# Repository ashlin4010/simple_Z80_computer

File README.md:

# Simple Z80 Computer
The goal of this project was to build a minimally complex Z80 computer capable of running CP/M. While I haven not yet ported CP/M, it should be capable of it.

This system is made of two boards, the upper board has the the CPU, RAM, ROM and UART. The lower board has Composite Video, USB Keyboard, USB to serial converter, Compact Flash and 8 indicator LEDs.

If you want to have a better understanding of how this system works you checkout the schematics or my [blog](https://blog.tephra.me/z80_sbc/).

## Specifications ##
* 64K Static RAM
* 32K ROM
* Z80 @ 4Mhz
* USB Keyboard via Raspberry Pi Zero
* Composite Video via Raspberry Pi Zero
* HDMI Video via Raspberry Pi Zero
* Support for 27256 or AT28C256 ROM
* Compact Flash
* 8 LED indicators
* Built-in USB to serial converter @ 9600 baud

## Raspberry Pi Zero (Optional) ##
As part of the project I wanted to have a composite video output however, there was not sufficient space to have a native composite video interface. As an alternative I have used a Raspberry Pi Zero running [pigfx](https://github.com/fbergama/pigfx) which acts as a terminal emulator providing a USB keyboard input and composite video output.

### Raspberry Pi Installation ###
To the underside of the PCB solder in the Raspberry Pi using the pins from a 2.54mm header so that the Pi is flat against the PCB. Only the circles and yellow need to be soldered. Back on the top side of the PCB you will see some pads that need to be connected to some test points on the Pi, connect them using some wire cuts offs.

## ROM Jumper Configuration ##

This system supports the W27C257, 27256 and AT28C256 ROM chips. The W27C257 and 27256 are read-only and need to have jumpers set in the topmost position. The AT28C256 is read/write and needs two jumpers in the lower position.

## Software Compiler ##
My assembler of choice for this project has been the [Retro Assembler](https://enginedesigns.net/retroassembler/) by Peter Tihanyi. There is a VSCode [plugin](https://marketplace.visualstudio.com/items?itemName=EngineDesigns.retroassembler) available.

## Serial Bootloader  ##
The early version of the monitor includes a utility "sboot" that will fetch data over the UART and store it in the lower 32k and jump to the start of memory.

For the serial bootloader to work you must be running the server utility that will provide the files for sboot to load. You can find it in ``software/server``.

The sboot command can be configured to auto start on boot by setting `UART_AUTO_BOOT` to True in `monitor.z80.asm` and re-building.

## Memory Address Space ##

This system has 64K of RAM and 32K of ROM. However, the Z80 can only ever address 64K at a time. When the system starts up the top 32K of memory maps to RAM, and the lower 32K maps to ROM. The system can, when ready, swap the lower 32K of ROM for RAM.

 ## IO Address Space ##

| Address | Device        | R/W | Description             |
|---------|---------------|-----|-------------------------|
| 0x10    | SIO           | R/W | UART A Data Register    |
| 0x11    | SIO           | R   | UART A Status Register  |
| 0x12    | SIO           | R/W | UART B Data Register    |
| 0x13    | SIO           | R   | UART B Status Register  |
| 0x20    | 8-bit Latch   | W   | LED Output              |
| 0x30-37 | Compact Flash | R/W | Compact Flash Registers |
| 0x70    | Flip-flop     | W   | RAM/ROM Page            |

## Schematics ##

### Z80 Main Board Schematics - [PDF](design_files/main_board/simple_Z80.pdf) ###

### Compact Flash & Raspberry Pi Board - [PDF](design_files/CompactFlash/CompactFlash.pdf) ###

## BOM ##

### Z80 Board ##

| Id | Designator                                              | Footprint                                                          | Quantity | Designation         | Supplier and ref |   |   |
|----|---------------------------------------------------------|--------------------------------------------------------------------|----------|---------------------|------------------|---|---|
| 1  | J2                                                      | PinHeader_1x04_P2.54mm_Vertical                                    | 1        | Conn_01x04_Male     |                  |   |   |
| 2  | C3,C2,C4,C5,C17,C12,C14,C6,C7,C16,C9,C13,C8,C10,C11,C15 | C_Disc_D3.0mm_W1.6mm_P2.50mm                                       | 16       | 0.1uf               |https://www.digikey.co.nz/en/products/detail/kemet/C320C104K5R5TA7303/3726160                  |   |   |
| 3  | R2,R1,R3,R4                                             | R_Axial_DIN0204_L3.6mm_D1.6mm_P7.62mm_Horizontal                   | 4        | 2k7                 |                  |   |   |
| 4  | R5                                                      | R_Axial_DIN0204_L3.6mm_D1.6mm_P7.62mm_Horizontal                   | 1        | 1k                  |                  |   |   |
| 5  | C1                                                      | C_Disc_D3.0mm_W1.6mm_P2.50mm                                       | 1        | 150pF               |https://www.digikey.co.nz/en/products/detail/vishay-beyschlag-draloric-bc-components/K151J15C0GF5TL2/286469                  |   |   |
| 6  | U1                                                      | DIP-40_W15.24mm_Socket                                             | 1        | Z80CPU              |                  |   |   |
| 7  | U7                                                      | DIP-40_W15.24mm                                                    | 1        | Z8440               |                  |   |   |
| 8  | U14, U2                                                 | DIP-28_W15.24mm                                                    | 1        | KM62256CLP          |                  |   |   |
| 9  | U13                                                     | DIP-20_W7.62mm_Socket                                              | 1        | 74LS374             |                  |   |   |
| 10 | U5                                                      | DIP-14_W7.62mm_Socket                                              | 1        | 74LS04              |                  |   |   |
| 11 | U9                                                      | DIP-16_W7.62mm_Socket                                              | 1        | 74LS161             |                  |   |   |
| 12 | U3                                                      | DIP_Socket-28_W11.9_W12.7_W15.24_W17.78_W18.5_3M_228-1277-00-0602J | 1        | 27256               |                  |   |   |
| 13 | X1                                                      | Oscillator_DIP-8                                                   | 1        | CXO_DIP8            |https://www.digikey.co.nz/en/products/detail/abracon-llc/ACH-8-000MHZ-EK/675379                  |   |   |
| 14 | U15                                                     | TO-92                                                              | 1        | DS1233              |https://www.digikey.co.nz/en/products/detail/analog-devices-inc-maxim-integrated/DS1233-5-T-R/1017808                  |   |   |
| 15 | D2                                                      | LED_D3.0mm                                                         | 1        | LED                 |                  |   |   |
| 16 | U11,U8                                                  | DIP-14_W7.62mm_Socket                                              | 2        | 74LS74              |                  |   |   |
| 17 | SW2                                                     | SW_THT_SK-12F17-G_7-0                                              | 1        | SW_SPDT             |https://www.digikey.co.nz/en/products/detail/c-k/SK-12F17-G-7/2747163                  |   |   |
| 18 | U4                                                      | DIP-14_W7.62mm_Socket                                              | 1        | 74LS00              |                  |   |   |
| 19 | SW1                                                     | SW_PUSH_6mm_H4.3mm                                                 | 1        | SW_Push             |https://www.digikey.co.nz/en/products/detail/cui-devices/TS02-66-70-BK-160-LCR-D/15634243                  |   |   |
| 20 | U6                                                      | DIP-16_W7.62mm_Socket                                              | 1        | 74LS138             |                  |   |   |
| 21 | J1                                                      | PinSocket_2x16_P2.54mm_Vertical                                    | 1        | Conn_01x32_Pin      |                  |   |   |
| 22 | J4                                                      | BarrelJack_CUI_PJ-037A                                             | 1        | Jack-DC             |https://www.digikey.co.nz/en/products/detail/cui-devices/PJ-037A/1644545                  |   |   |
| 23 | U12                                                     | DIP-14_W7.62mm_Socket                                              | 1        | 74LS32              |                  |   |   |
| 24 | J7                                                      | PinSocket_2x06_P2.54mm_Vertical                                    | 1        | Conn_01x12_Male     |                  |   |   |
| 25 | J3                                                      | PinHeader_2x03_P2.54mm_Vertical                                    | 1        | Conn_02x03_Odd_Even |                  |   |   |

### CompactFlash ##

| Id | Designator                      | Footprint                                             | Quantity | Designation       | Supplier and ref |   |   |
|----|---------------------------------|-------------------------------------------------------|----------|-------------------|------------------|---|---|
| 1  | R2                              | R_Axial_DIN0204_L3.6mm_D1.6mm_P7.62mm_Horizontal      | 1        | 100R              |                  |   |   |
| 2  | J2                              | PinHeader_2x06_P2.54mm_Vertical                       | 1        | Conn_01x12_Male   |                  |   |   |
| 3  | J7,J8                           | SolderWirePad_1x01_SMD_1x2mm                          | 2        | Conn_01x01_Pin    |                  |   |   |
| 4  | R8,R9,R7,R10                    | R_Axial_DIN0204_L3.6mm_D1.6mm_P7.62mm_Horizontal      | 4        | 10k               |                  |   |   |
| 5  | J5                              | SWITCHCRAFT_PJRAN1X1U04X                              | 1        | RCA_Video         |https://www.digikey.co.nz/en/products/detail/switchcraft-inc/PJRAN1X1U04X/969899                         |   |   |
| 6  | U1                              | CF-Card_101D-TAAB-R01                                 | 1        | Compact_Flash     |https://www.digikey.co.nz/en/products/detail/attend-technology/101D-TAAB-R01/17633884                    |   |   |
| 7  | U2                              | DIP-20_W7.62mm                                        | 1        | 74LS541           |                  |   |   |
| 8  | Q2,Q1                           | TO-92_Inline                                          | 2        | 2N7000            |https://www.digikey.co.nz/en/products/detail/diotec-semiconductor/2N7000/13164314                        |   |   |
| 9  | D2,D8,D6,D1,D4,D7,D5,D9,D3      | LED_D3.0mm_Horizontal_O1.27mm_Z2.0mm                  | 9        | LED               |                  |   |   |
| 10 | R1,R5,R6,R3,R4                  | R_Axial_DIN0204_L3.6mm_D1.6mm_P7.62mm_Horizontal      | 5        | 1K                |                  |   |   |
| 11 | U3                              | SOP-8_3.9x4.9mm_P1.27mm                               | 1        | CH340N            |https://vi.aliexpress.com/item/1005004980156804.html                                                     |   |   |
| 12 | R19,R20                         | R_0805_2012Metric                                     | 2        | 1k                |https://www.digikey.co.nz/en/products/detail/stackpole-electronics-inc/RNCP0805FTD1K00/2240229           |   |   |
| 13 | R14,R15,R18,R11,R13,R16,R17,R12 | R_Axial_DIN0204_L3.6mm_D1.6mm_P7.62mm_Horizontal      | 8        | 1k                |                  |   |   |
| 14 | J1                              | Raspberry_Pi_Zero_Socketed_THT_FaceDown_MountingHoles | 1        | Raspberry_Pi_Zero |                  |   |   |
| 15 | J4                              | PinSocket_2x16_P2.54mm_Vertical                       | 1        | Conn_01x32_Pin    |                  |   |   |
| 16 | J6                              | USB_Mini-B_Wuerth_65100516121_Horizontal              | 1        | USB_B_Micro       |https://www.digikey.co.nz/en/products/detail/amphenol-cs-commercial-products/GMSB0532112YEU/13683104     |   |   |
| 17 | J3                              | 629104190121                                          | 1        | USB_A             |https://www.digikey.co.nz/en/products/detail/w%C3%BCrth-elektronik/629104190121/6644275                  |   |   |
| 18 | J10                             | PinSocket_1x04_P2.54mm_Vertical                       | 1        | Conn_01x04_Pin    |                  |   |   |
| 19 | C1                              | C_Disc_D3.0mm_W1.6mm_P2.50mm                          | 1        | 100pF             |                  |   |   |
| 20 | C2                              | C_0805_2012Metric                                     | 1        | 100nF             |https://www.digikey.co.nz/en/products/detail/samsung-electro-mechanics/CL21B104KBCNNNC/3886661           |   |   |

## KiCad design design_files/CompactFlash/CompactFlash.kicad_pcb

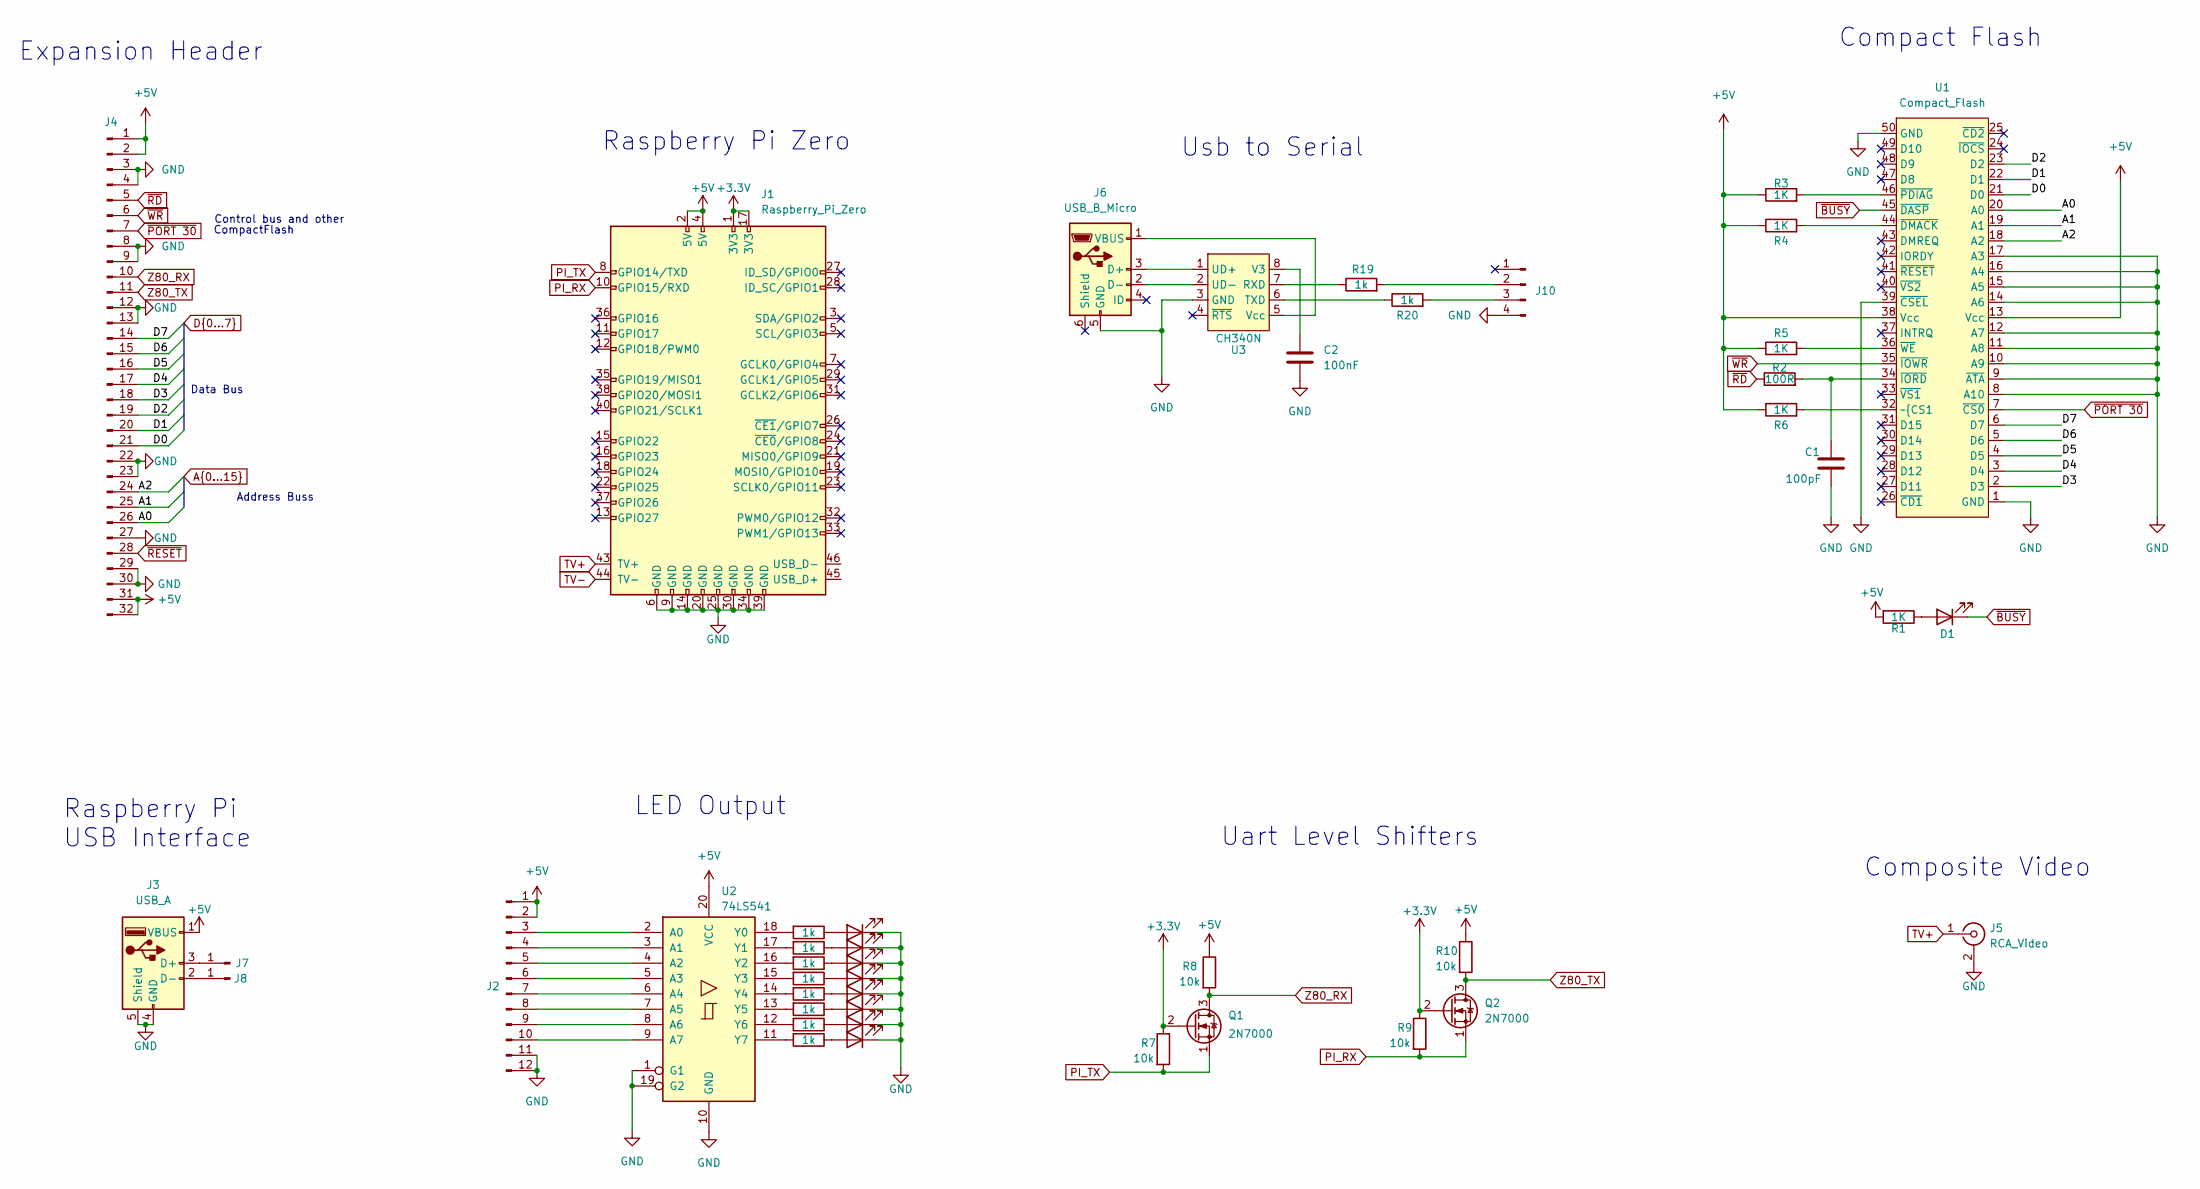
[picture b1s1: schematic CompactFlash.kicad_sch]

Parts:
C1: 100pF; C_Disc_D3.0mm_W1.6mm_P2.50mm
C2: 100nF; C_0805_2012Metric
D1, D2, D3, D4, D5, D6, D7, D8, D9: LED; LED_D3.0mm_Horizontal_O1.27mm_Z2.0mm
J1: Raspberry_Pi_Zero; Raspberry_Pi_Zero_Socketed_THT_FaceDown_MountingHoles
J2: Conn_01x12_Male; PinHeader_2x06_P2.54mm_Vertical
J3: USB_A; 629104190121
J4: Conn_01x32_Pin; PinSocket_2x16_P2.54mm_Vertical
J5: RCA_Video; SWITCHCRAFT_PJRAN1X1U04X
J6: USB_B_Micro; USB_Mini-B_Wuerth_65100516121_Horizontal
J7, J8: Conn_01x01_Pin; SolderWirePad_1x01_SMD_1x2mm
J10: Conn_01x04_Pin; PinSocket_1x04_P2.54mm_Vertical
Q1, Q2: 2N7000; TO-92_Inline
R1, R3, R4, R5, R6: 1K; R_Axial_DIN0204_L3.6mm_D1.6mm_P7.62mm_Horizontal
R2: 100R; R_Axial_DIN0204_L3.6mm_D1.6mm_P7.62mm_Horizontal
R7, R8, R9, R10: 10k; R_Axial_DIN0204_L3.6mm_D1.6mm_P7.62mm_Horizontal
R11, R12, R13, R14, R15, R16, R17, R18: 1k; R_Axial_DIN0204_L3.6mm_D1.6mm_P7.62mm_Horizontal
R19, R20: 1k; R_0805_2012Metric
U1: Compact_Flash; CF-Card_3M_N7E50-E516xx-30
U2: 74LS541; DIP-20_W7.62mm
U3: CH340N; SOP-8_3.9x4.9mm_P1.27mm

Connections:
+3.3V: J1.1 (3V3), J1.17 (3V3), Q1.2 (G), Q2.2 (G), R7.1, R9.1
+5V: J1.2 (5V), J1.4 (5V), J2.1, J2.2, J3.1 (VBUS), J4.1, J4.2, J4.31, J4.32, R1.2, R3.1, R4.1, R5.1, R6.1, R8.1, R10.1, U1.13 (Vcc), U1.38 (Vcc), U2.20 (VCC)
/A0: J4.26, U1.20 (A0)
/A1: J4.25, U1.19 (A1)
/A2: J4.24, U1.18 (A2)
/D0: J4.21, U1.21 (D0)
/D1: J4.20, U1.22 (D1)
/D2: J4.19, U1.23 (D2)
/D3: J4.18, U1.2 (D3)
/D4: J4.17, U1.3 (D4)
/D5: J4.16, U1.4 (D5)
/D6: J4.15, U1.5 (D6)
/D7: J4.14, U1.6 (D7)
GND: C1.2, C2.1, D2.1 (K), D3.1 (K), D4.1 (K), D5.1 (K), D6.1 (K), D7.1 (K), D8.1 (K), D9.1 (K), J1.6 (GND), J1.9 (GND), J1.14 (GND), J1.20 (GND), J1.25 (GND), J1.30 (GND), J1.34 (GND), J1.39 (GND), J2.11, J2.12, J3.4 (GND), J3.5 (Shield), J4.3, J4.4, J4.8, J4.9, J4.12, J4.13, J4.22, J4.23, J4.27, J4.29, J4.30, J5.2 (Ext), J6.5 (GND), J10.4, U1.1 (GND), U1.8 (A10), U1.9 (~ATA), U1.10 (A9), U1.11 (A8), U1.12 (A7), U1.14 (A6), U1.15 (A5), U1.16 (A4), U1.17 (A3), U1.39 (~CSEL), U1.50 (GND), U2.1 (G1), U2.10 (GND), U2.19 (G2), U3.3 (GND)
unnamed: D1.2 (A), R1.1
unnamed: D2.2 (A), R11.1
unnamed: D3.2 (A), R12.1
unnamed: D4.2 (A), R13.1
unnamed: D5.2 (A), R14.1
unnamed: D6.2 (A), R15.1
unnamed: D7.2 (A), R16.1
unnamed: D8.2 (A), R17.1
unnamed: D9.2 (A), R18.1
unnamed: J2.3, U2.2 (A0)
unnamed: J2.4, U2.3 (A1)
unnamed: J2.5, U2.4 (A2)
unnamed: J2.6, U2.5 (A3)
unnamed: J2.7, U2.6 (A4)
unnamed: J2.8, U2.7 (A5)
unnamed: J2.9, U2.8 (A6)
unnamed: J2.10, U2.9 (A7)
unnamed: J3.3 (D+), J7.1
unnamed: J3.2 (D-), J8.1
unnamed: J6.3 (D+), U3.1 (UD+)
unnamed: J6.2 (D-), U3.2 (UD-)
unnamed: J6.1 (VBUS), U3.5 (Vcc)
unnamed: J10.2, R19.2
unnamed: J10.3, R20.2
unnamed: R6.2, U1.32 (~{CS1)
unnamed: R4.2, U1.44 (~DMACK)
unnamed: C1.1, R2.2, U1.34 (~IORD)
unnamed: R3.2, U1.46 (~PDIAG)
unnamed: R5.2, U1.36 (~WE)
unnamed: R11.2, U2.18 (Y0)
unnamed: R12.2, U2.17 (Y1)
unnamed: R13.2, U2.16 (Y2)
unnamed: R14.2, U2.15 (Y3)
unnamed: R15.2, U2.14 (Y4)
unnamed: R16.2, U2.13 (Y5)
unnamed: R17.2, U2.12 (Y6)
unnamed: R18.2, U2.11 (Y7)
unnamed: R19.1, U3.7 (RXD)
unnamed: R20.1, U3.6 (TXD)
unnamed: C2.2, U3.8 (V3)
PI_RX: J1.10 (GPIO15/RXD), Q2.1 (S), R9.2
PI_TX: J1.8 (GPIO14/TXD), Q1.1 (S), R7.2
TV+: J1.43 (TV+), J5.1 (In)
TV-: J1.44 (TV-)
Z80_RX: J4.10, Q1.3 (D), R8.2
Z80_TX: J4.11, Q2.3 (D), R10.2
~BUSY: D1.1 (K), U1.45 (~DASP)
~PORT 30: J4.7, U1.7 (~CS0)
~RD: J4.5, R2.1
~RESET: J4.28
~WR: J4.6, U1.35 (~IOWR)

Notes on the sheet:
Usb to Serial
Compact Flash
CompactFlash
Control bus and other
Raspberry Pi USB Interface
Composite Video
Uart Level Shifters
Data Bus
Address Buss
LED Output
Raspberry Pi Zero
Expansion Header

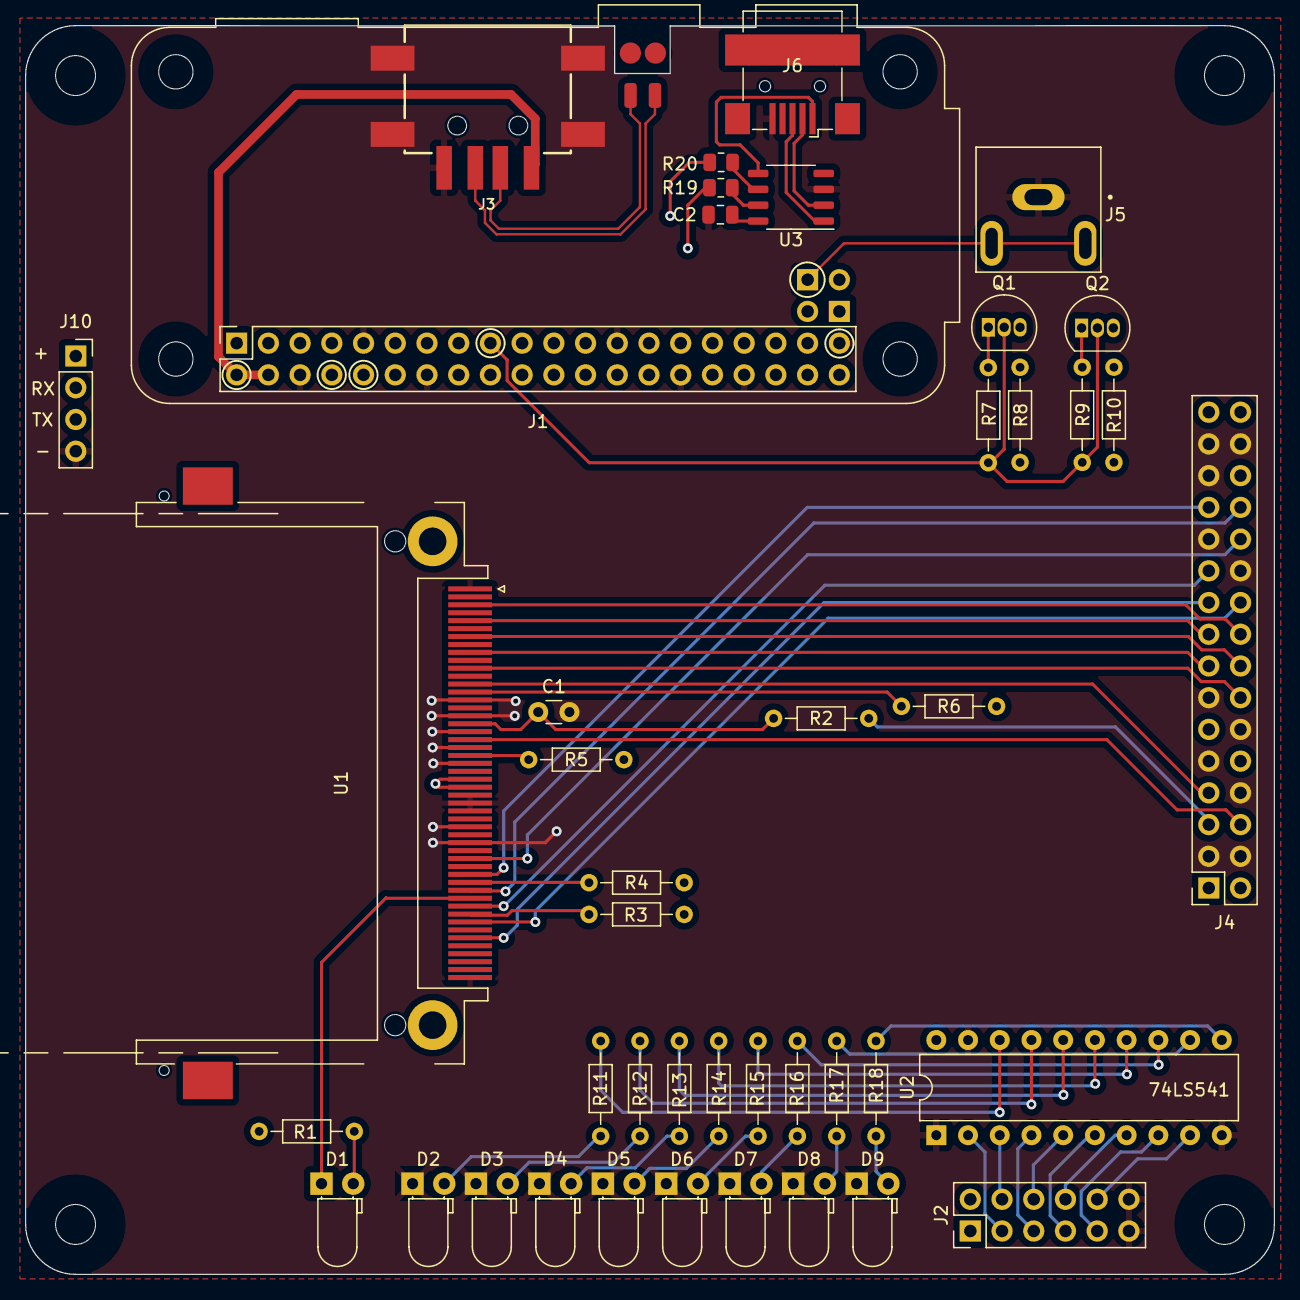
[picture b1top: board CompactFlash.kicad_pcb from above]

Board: 4 copper layers, 100.0 x 100.0 mm, 49 parts (0 on the bottom side), 63 nets.

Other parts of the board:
H1, H2, H3, H4: MountingHole; MountingHole_3.2mm_M3

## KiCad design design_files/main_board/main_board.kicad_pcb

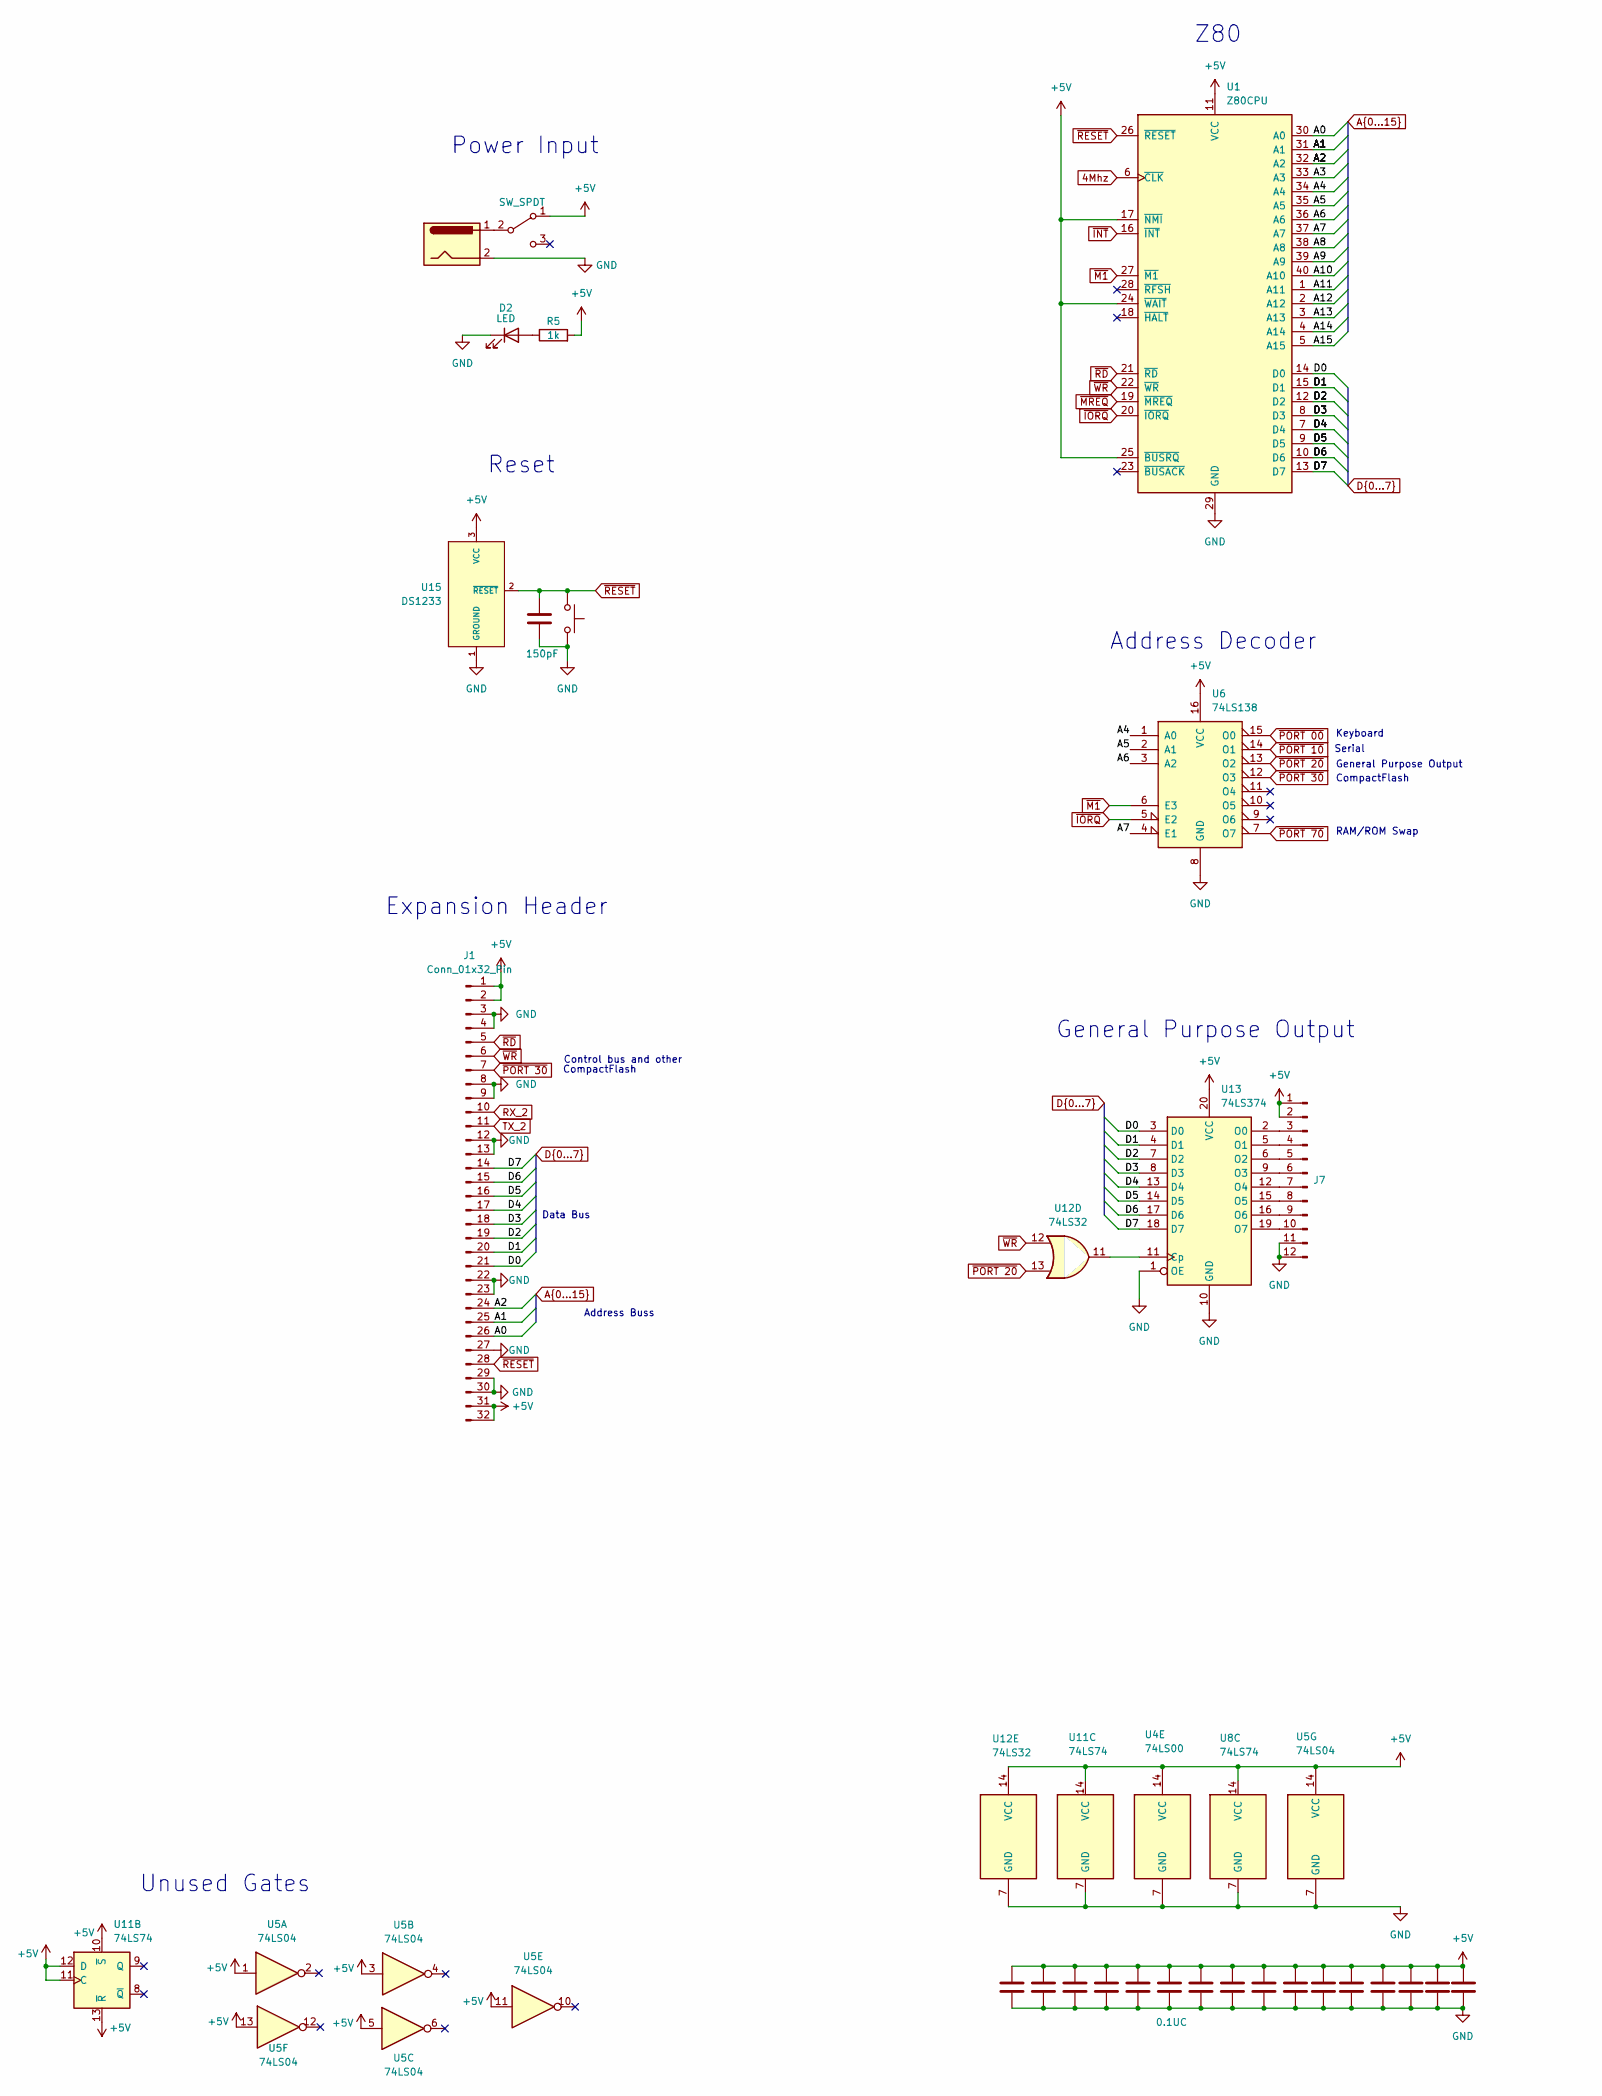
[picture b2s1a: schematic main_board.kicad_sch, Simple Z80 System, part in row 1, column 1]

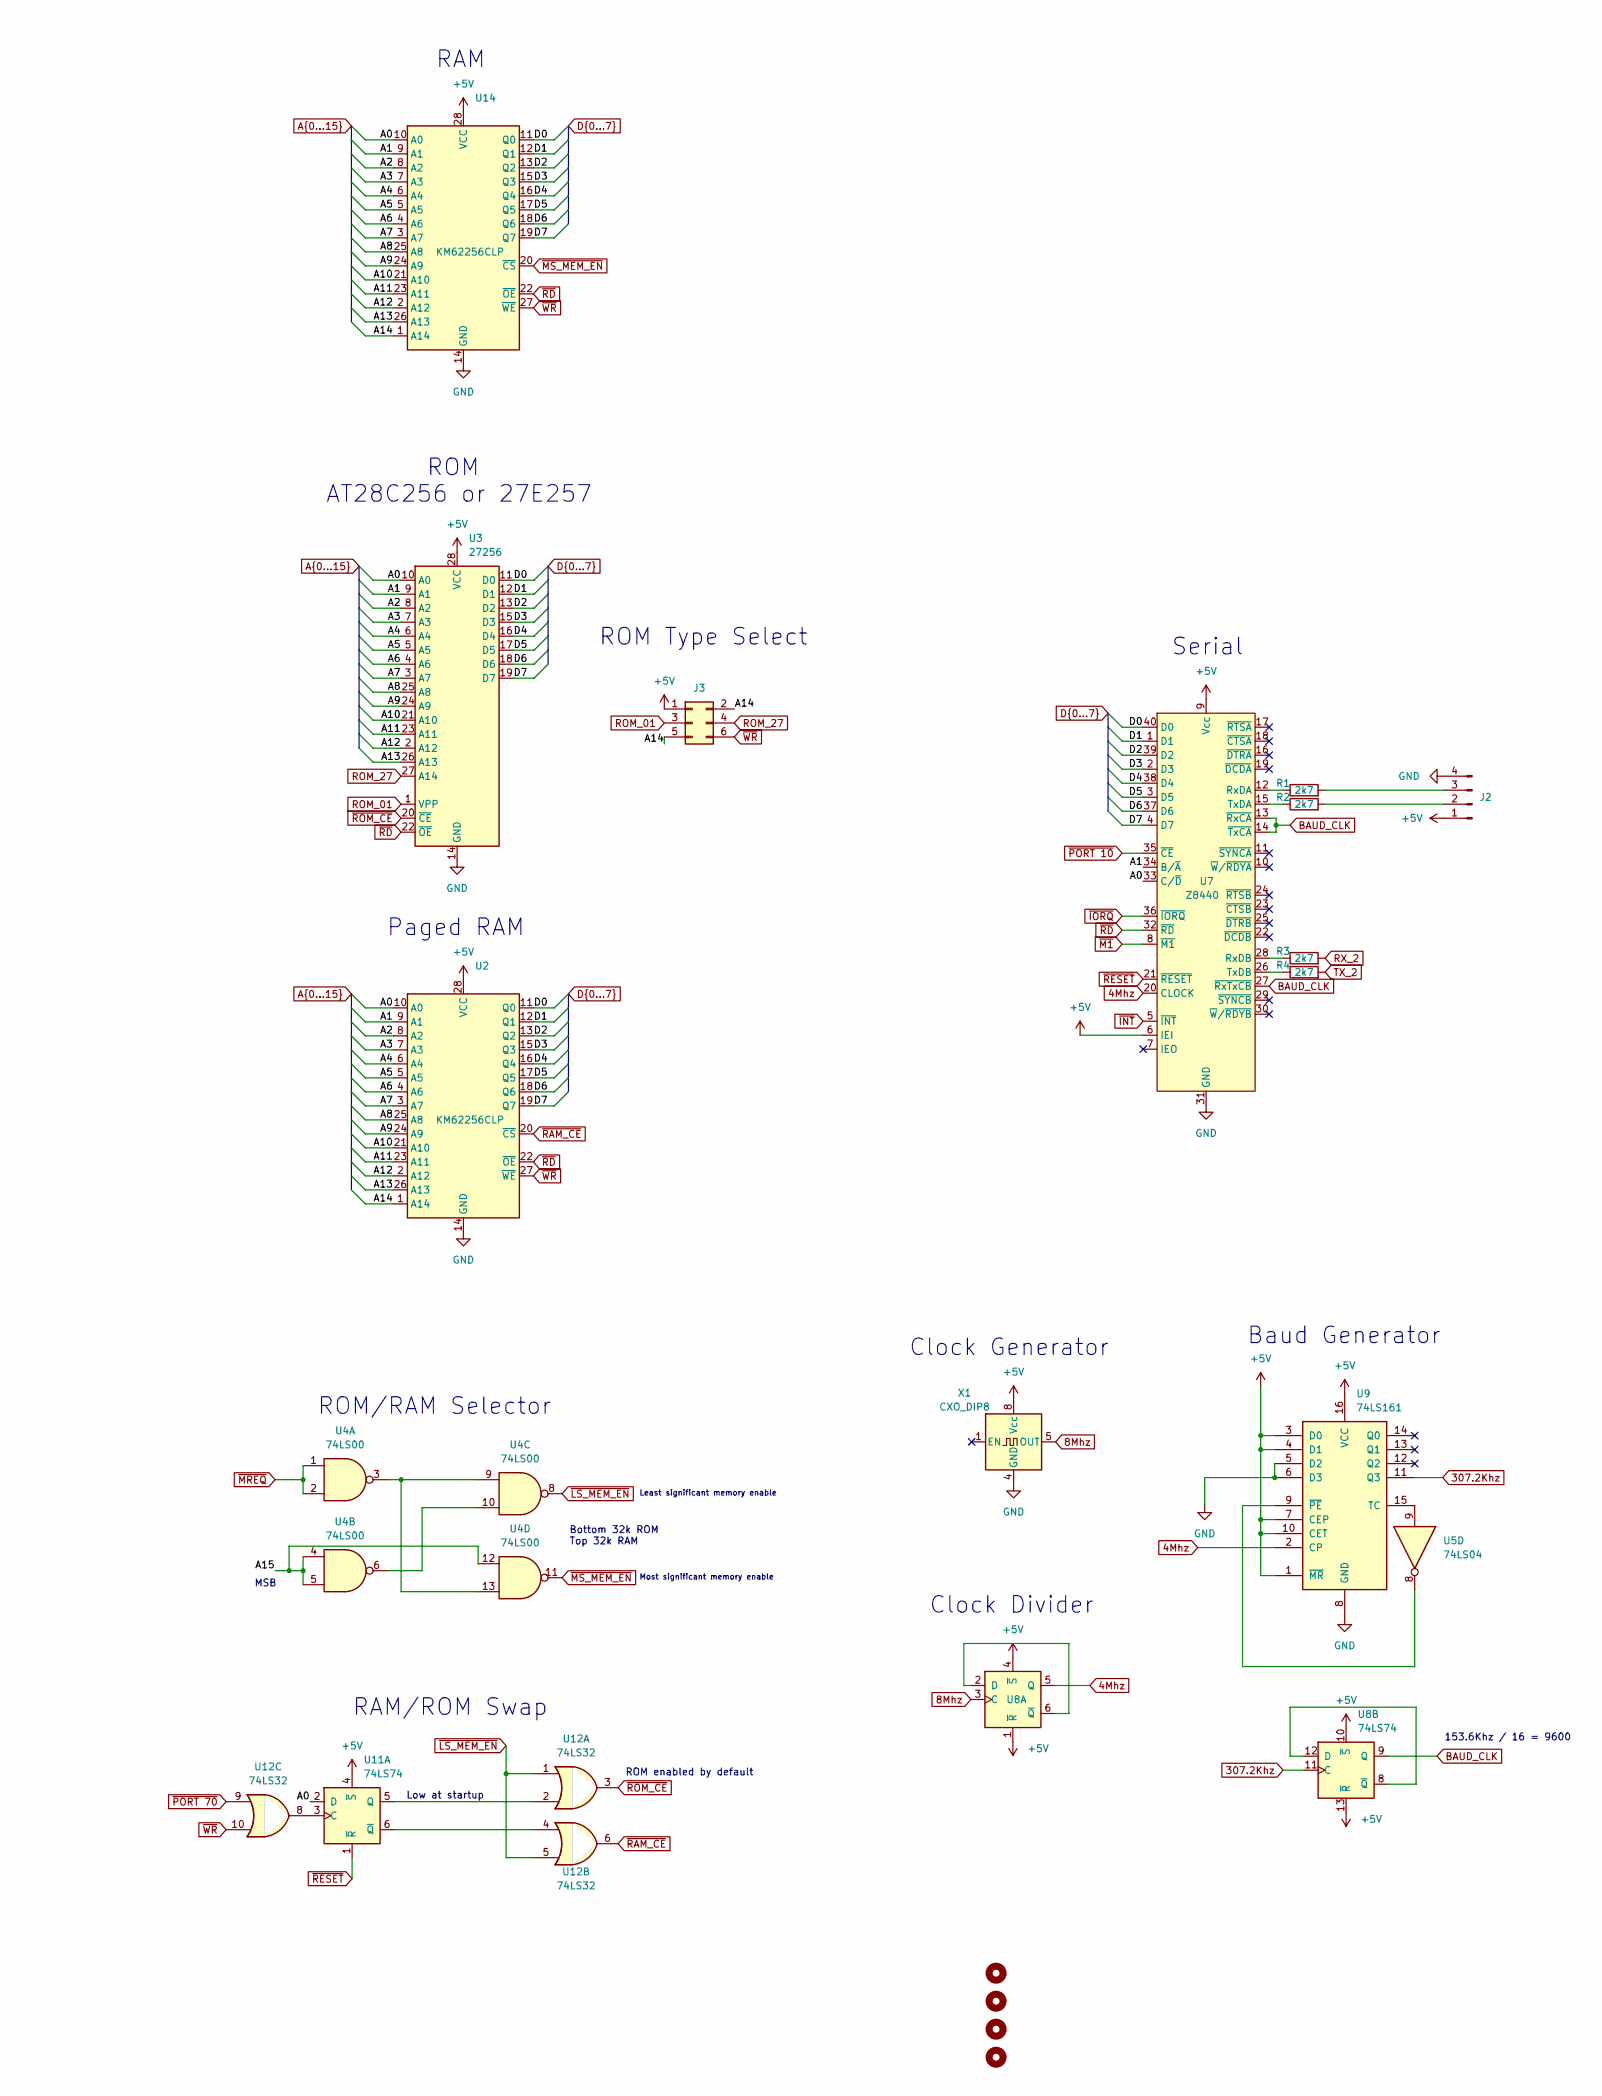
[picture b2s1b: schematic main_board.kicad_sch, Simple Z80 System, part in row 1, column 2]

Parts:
C1: 150pF; C_Disc_D3.0mm_W1.6mm_P2.50mm
C2, C3, C4, C5, C6, C7, C8, C9, C10, C11, C12, C13, C14, C15, C16, C17: 0.1UC; C_Disc_D3.0mm_W1.6mm_P2.50mm
D2: LED; LED_D3.0mm
H1, H2, H3, H4: MountingHole; MountingHole_3.2mm_M3
J1: Conn_01x32_Pin; PinSocket_2x16_P2.54mm_Vertical
J2: Conn_01x04_Male; PinHeader_1x04_P2.54mm_Vertical
J3: Conn_02x03_Odd_Even; PinHeader_2x03_P2.54mm_Vertical
J4: Jack-DC; BarrelJack_CUI_PJ-037A
J7: Conn_01x12_Male; PinSocket_2x06_P2.54mm_Vertical
R1, R2, R3, R4: 2k7; R_Axial_DIN0204_L3.6mm_D1.6mm_P7.62mm_Horizontal
R5: 1k; R_Axial_DIN0204_L3.6mm_D1.6mm_P7.62mm_Horizontal
SW1: SW_Push; SW_PUSH_6mm_H4.3mm
SW2: SW_SPDT; SW_THT_SK-12F17-G_7-0
U1: Z80CPU; DIP-40_W15.24mm_Socket
U2: KM62256CLP; DIP-28_W15.24mm_Socket
U3: 27256; DIP_Socket-28_W11.9_W12.7_W15.24_W17.78_W18.5_3M_228-1277-0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
U4: 74LS00; DIP-14_W7.62mm_Socket
U5: 74LS04; DIP-14_W7.62mm_Socket
U6: 74LS138; DIP-16_W7.62mm_Socket
U7: Z8440; DIP-40_W15.24mm
U8, U11: 74LS74; DIP-14_W7.62mm_Socket
U9: 74LS161; DIP-16_W7.62mm_Socket
U12: 74LS32; DIP-14_W7.62mm_Socket
U13: 74LS374; DIP-20_W7.62mm_Socket
U14: KM62256CLP; DIP-28_W15.24mm
U15: DS1233; TO-92
X1: CXO_DIP8; Oscillator_DIP-8

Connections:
4Mhz: U1.6 (~CLK), U7.20 (CLOCK), U8.5 (Q), U9.2 (CP)
8Mhz: U8.3 (C), X1.5 (OUT)
307.2Khz: U8.11 (C), U9.11 (Q3)
+5V: C2.1, C3.1, C4.1, C5.1, C6.1, C7.1, C8.1, C9.1, C10.1, C11.1, C12.1, C13.1, C14.1, C15.1, C16.1, C17.1, J1.1, J1.2, J1.31, J1.32, J2.1, J3.1, J7.1, J7.2, R5.2, SW2.1 (A), U1.11 (VCC), U1.17 (~NMI), U1.24 (~WAIT), U1.25 (~BUSRQ), U2.28 (VCC), U3.28 (VCC), U4.14 (VCC), U5.1, U5.3, U5.5, U5.11, U5.13, U5.14 (VCC), U6.16 (VCC), U7.6 (IEI), U7.9 (Vcc), U8.1 (~R), U8.4 (~S), U8.10 (~S), U8.13 (~R), U8.14 (VCC), U9.1 (~MR), U9.3 (D0), U9.4 (D1), U9.7 (CEP), U9.10 (CET), U9.16 (VCC), U11.4 (~S), U11.10 (~S), U11.11 (C), U11.12 (D), U11.13 (~R), U11.14 (VCC), U12.14 (VCC), U13.20 (VCC), U14.28 (VCC), U15.3 (VCC), X1.8 (Vcc)
/A0: J1.26, U1.30 (A0), U2.10 (A0), U3.10 (A0), U7.33 (C/~D), U11.2 (D), U14.10 (A0)
/A1: J1.25, U1.31 (A1), U2.9 (A1), U3.9 (A1), U7.34 (B/~A), U14.9 (A1)
/A2: J1.24, U1.32 (A2), U2.8 (A2), U3.8 (A2), U14.8 (A2)
/A3: U1.33 (A3), U2.7 (A3), U3.7 (A3), U14.7 (A3)
/A4: U1.34 (A4), U2.6 (A4), U3.6 (A4), U6.1 (A0), U14.6 (A4)
/A5: U1.35 (A5), U2.5 (A5), U3.5 (A5), U6.2 (A1), U14.5 (A5)
/A6: U1.36 (A6), U2.4 (A6), U3.4 (A6), U6.3 (A2), U14.4 (A6)
/A7: U1.37 (A7), U2.3 (A7), U3.3 (A7), U6.4 (E1), U14.3 (A7)
/A8: U1.38 (A8), U2.25 (A8), U3.25 (A8), U14.25 (A8)
/A9: U1.39 (A9), U2.24 (A9), U3.24 (A9), U14.24 (A9)
/A10: U1.40 (A10), U2.21 (A10), U3.21 (A10), U14.21 (A10)
/A11: U1.1 (A11), U2.23 (A11), U3.23 (A11), U14.23 (A11)
/A12: U1.2 (A12), U2.2 (A12), U3.2 (A12), U14.2 (A12)
/A13: U1.3 (A13), U2.26 (A13), U3.26 (A13), U14.26 (A13)
/A14: J3.2, J3.5, U1.4 (A14), U2.1 (A14), U14.1 (A14)
/A15: U1.5 (A15), U4.4, U4.5, U4.12
/D0: J1.21, U1.14 (D0), U2.11 (Q0), U3.11 (D0), U7.40 (D0), U13.3 (D0), U14.11 (Q0)
/D1: J1.20, U1.15 (D1), U2.12 (Q1), U3.12 (D1), U7.1 (D1), U13.4 (D1), U14.12 (Q1)
/D2: J1.19, U1.12 (D2), U2.13 (Q2), U3.13 (D2), U7.39 (D2), U13.7 (D2), U14.13 (Q2)
/D3: J1.18, U1.8 (D3), U2.15 (Q3), U3.15 (D3), U7.2 (D3), U13.8 (D3), U14.15 (Q3)
/D4: J1.17, U1.7 (D4), U2.16 (Q4), U3.16 (D4), U7.38 (D4), U13.13 (D4), U14.16 (Q4)
/D5: J1.16, U1.9 (D5), U2.17 (Q5), U3.17 (D5), U7.3 (D5), U13.14 (D5), U14.17 (Q5)
/D6: J1.15, U1.10 (D6), U2.18 (Q6), U3.18 (D6), U7.37 (D6), U13.17 (D6), U14.18 (Q6)
/D7: J1.14, U1.13 (D7), U2.19 (Q7), U3.19 (D7), U7.4 (D7), U13.18 (D7), U14.19 (Q7)
BAUD_CLK: U7.13 (~RxCA), U7.14 (~TxCA), U7.27 (~RxTxCB), U8.9 (Q)
GND: C1.2, C2.2, C3.2, C4.2, C5.2, C6.2, C7.2, C8.2, C9.2, C10.2, C11.2, C12.2, C13.2, C14.2, C15.2, C16.2, C17.2, D2.1 (K), J1.3, J1.4, J1.8, J1.9, J1.12, J1.13, J1.22, J1.23, J1.27, J1.29, J1.30, J2.4, J4.2, J7.11, J7.12, SW1.2, U1.29 (GND), U2.14 (GND), U3.14 (GND), U4.7 (GND), U5.7 (GND), U6.8 (GND), U7.31 (GND), U8.7 (GND), U9.5 (D2), U9.6 (D3), U9.8 (GND), U11.7 (GND), U12.7 (GND), U13.1 (OE), U13.10 (GND), U14.14 (GND), U15.1 (GROUND), X1.4 (GND)
unnamed: D2.2 (A), R5.1
unnamed: J2.2, R2.2
unnamed: J2.3, R1.2
unnamed: J7.3, U13.2 (O0)
unnamed: J7.4, U13.5 (O1)
unnamed: J7.5, U13.6 (O2)
unnamed: J7.6, U13.9 (O3)
unnamed: J7.7, U13.12 (O4)
unnamed: J7.8, U13.15 (O5)
unnamed: J7.9, U13.16 (O6)
unnamed: J7.10, U13.19 (O7)
unnamed: J4.1, SW2.2 (B)
unnamed: U4.6, U4.10
unnamed: U4.3, U4.9, U4.13
unnamed: R1.1, U7.12 (RxDA)
unnamed: R3.1, U7.28 (RxDB)
unnamed: R2.1, U7.15 (TxDA)
unnamed: R4.1, U7.26 (TxDB)
unnamed: U8.2 (D), U8.6 (~Q)
unnamed: U8.8 (~Q), U8.12 (D)
unnamed: U5.9, U9.15 (TC)
unnamed: U5.8, U9.9 (~PE)
unnamed: U11.3 (C), U12.8
unnamed: U11.5 (Q), U12.2
unnamed: U11.6 (~Q), U12.4
unnamed: U12.11, U13.11 (Cp)
ROM_01: J3.3, U3.1 (VPP)
ROM_27: J3.4, U3.27 (A14)
RX_2: J1.10, R3.2
TX_2: J1.11, R4.2
~INT: U1.16 (~INT), U7.5 (~INT)
~IORQ: U1.20 (~IORQ), U6.5 (E2), U7.36 (~IORQ)
~LS_MEM_EN: U4.8, U12.1, U12.5
~M1: U1.27 (~M1), U6.6 (E3), U7.8 (~M1)
~MREQ: U1.19 (~MREQ), U4.1, U4.2
~MS_MEM_EN: U4.11, U14.20 (~CS)
~PORT 00: U6.15 (O0)
~PORT 10: U6.14 (O1), U7.35 (~CE)
~PORT 20: U6.13 (O2), U12.13
~PORT 30: J1.7, U6.12 (O3)
~PORT 70: U6.7 (O7), U12.9
~RAM_CE: U2.20 (~CS), U12.6
~RD: J1.5, U1.21 (~RD), U2.22 (~OE), U3.22 (~OE), U7.32 (~RD), U14.22 (~OE)
~RESET: C1.1, J1.28, SW1.1, U1.26 (~RESET), U7.21 (~RESET), U11.1 (~R), U15.2 (~RESET)
~ROM_CE: U3.20 (~CE), U12.3
~WR: J1.6, J3.6, U1.22 (~WR), U2.27 (~WE), U12.10, U12.12, U14.27 (~WE)

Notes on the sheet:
RAM/ROM Swap
Most significant memory enable
ROM/RAM Selector
RAM
Z80
Reset
Serial
ROM Type Select
Address Buss
Baud Generator
Least significant memory enable
CompactFlash
Clock Generator
General Purpose Output
Bottom 32k ROM Top 32k RAM
Paged RAM
MSB
Clock Divider
Keyboard
Low at startup
Data Bus
153.6Khz / 16 = 9600
ROM AT28C256 or 27E257
Expansion Header
Address Decoder
ROM enabled by default
Unused Gates
Control bus and other
Power Input
